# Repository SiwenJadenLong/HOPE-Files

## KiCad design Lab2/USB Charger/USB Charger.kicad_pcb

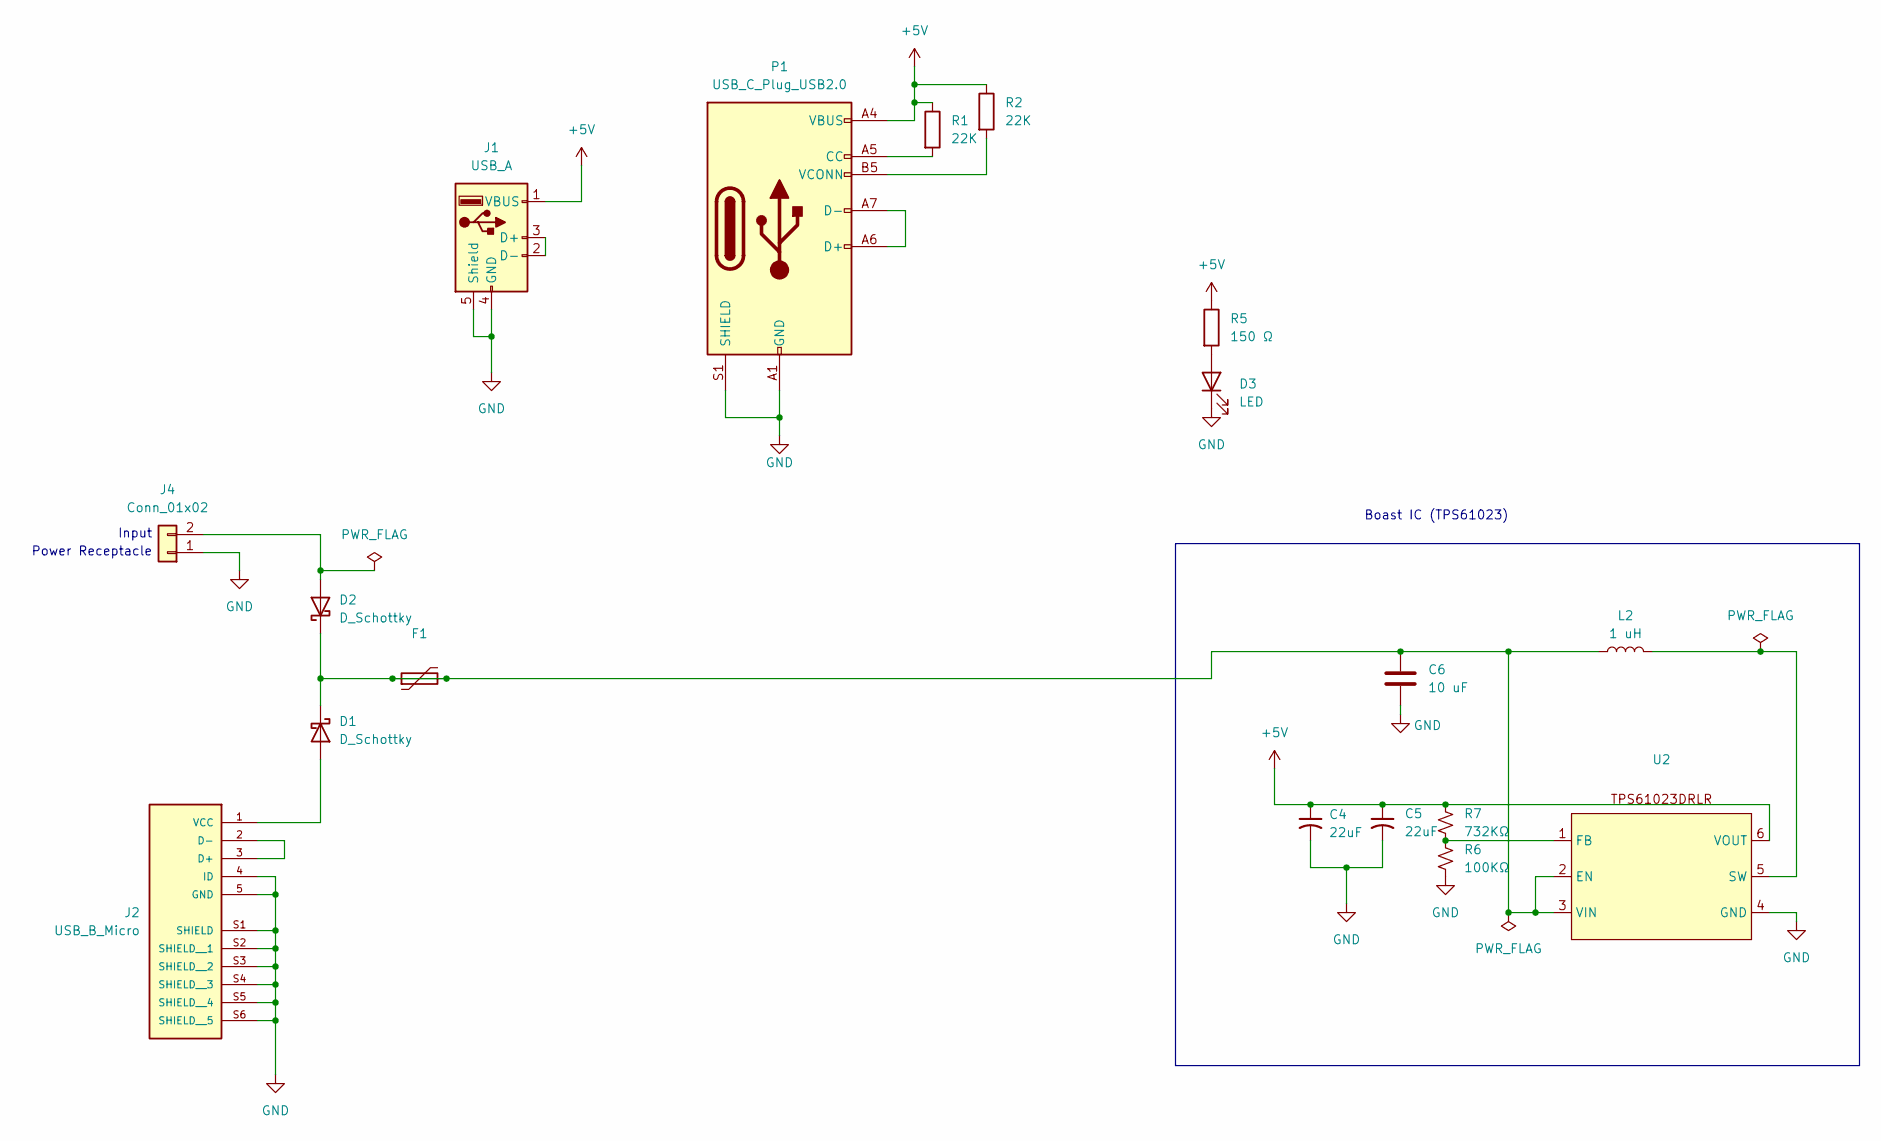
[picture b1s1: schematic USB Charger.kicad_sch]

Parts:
C4, C5: 22uF; C_0603_1608Metric_Pad1.08x0.95mm_HandSolder
C6: 10 uF; C_0402_1005Metric
D1, D2: D_Schottky; D_SMA-SMB_Universal_Handsoldering
D3: LED; LED_0805_2012Metric_Pad1.15x1.40mm_HandSolder
F1: Polyfuse; Fuse_1812_4532Metric_Pad1.30x3.40mm_HandSolder
J1: USB_A; USB_A_Receptacle_GCT_USB1046
J2: USB_B_Micro; AMPHENOL_10118192-0002LF; PARTREV B
J4: Conn_01x02; PinHeader_1x02_P2.54mm_Vertical
L2: 1 uH; SRP6540-1R0M
P1: USB_C_Plug_USB2.0; USB_C_Receptacle_GCT_USB4105-xx-A_16P_TopMnt_Horizontal
R1, R2: 22K; R_0603_1608Metric
R5: 150 Ω; R_0805_2012Metric
R6: 100KΩ; R_0402_1005Metric
R7: 732KΩ; R_0402_1005Metric
U2: SOT-666

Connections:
+5V: C4.1, C5.1, J1.1 (VBUS), P1.A4 (VBUS), P1.A9 (VBUS), P1.B4 (VBUS), P1.B9 (VBUS), R1.1, R2.1, R5.1, R7.1, U2.6 (VOUT)
GND: C4.2, C5.2, C6.2, D3.1 (K), J1.4 (GND), J1.5 (Shield), J2.4 (ID), J2.5 (GND), J2.S1 (SHIELD), J2.S2 (SHIELD__1), J2.S3 (SHIELD__2), J2.S4 (SHIELD__3), J2.S5 (SHIELD__4), J2.S6 (SHIELD__5), J4.1, P1.A1 (GND), P1.A12 (GND), P1.B1 (GND), P1.B12 (GND), P1.S1 (SHIELD), R6.2, U2.4 (GND)
unnamed: D1.2 (A), J2.1 (VCC)
unnamed: C6.1, D1.1 (K), D2.1 (K), F1.1, F1.2, L2.1, U2.2 (EN), U2.3 (VIN)
unnamed: D2.2 (A), J4.2
unnamed: D3.2 (A), R5.2
unnamed: J1.2 (D-), J1.3 (D+)
unnamed: J2.2 (D-), J2.3 (D+)
unnamed: P1.A5 (CC), R1.2
unnamed: P1.A6 (D+), P1.A7 (D-)
unnamed: P1.B5 (VCONN), R2.2
unnamed: R6.1, R7.2, U2.1 (FB)
unnamed: L2.2, U2.5 (SW)

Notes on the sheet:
Input
Power Receptacle
Boast IC (TPS61023)

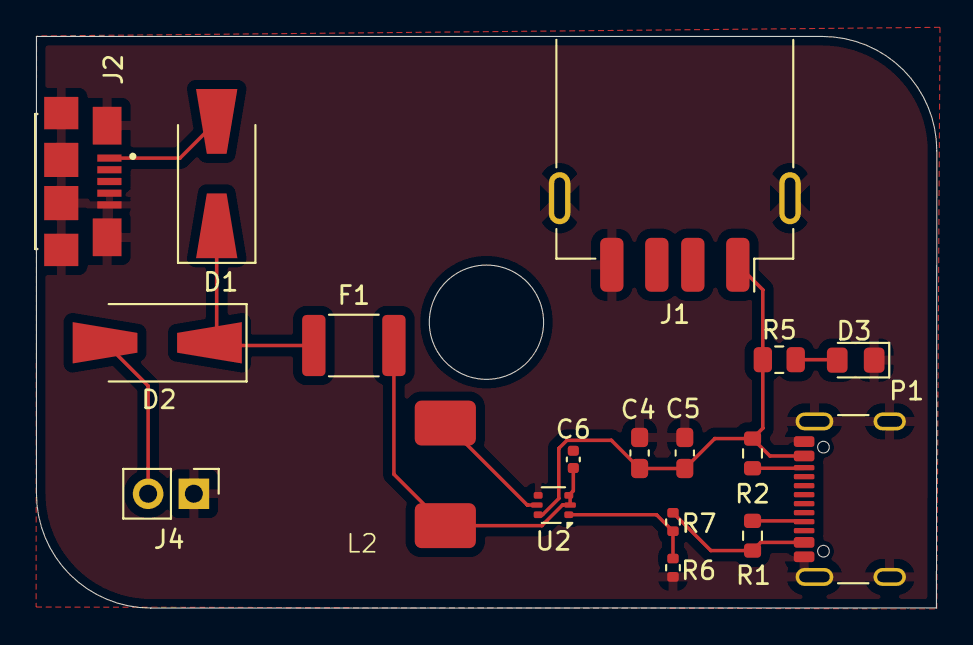
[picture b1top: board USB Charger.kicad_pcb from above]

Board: 2 copper layers, 50.0 x 31.8 mm, 18 parts (0 on the bottom side), 13 nets.

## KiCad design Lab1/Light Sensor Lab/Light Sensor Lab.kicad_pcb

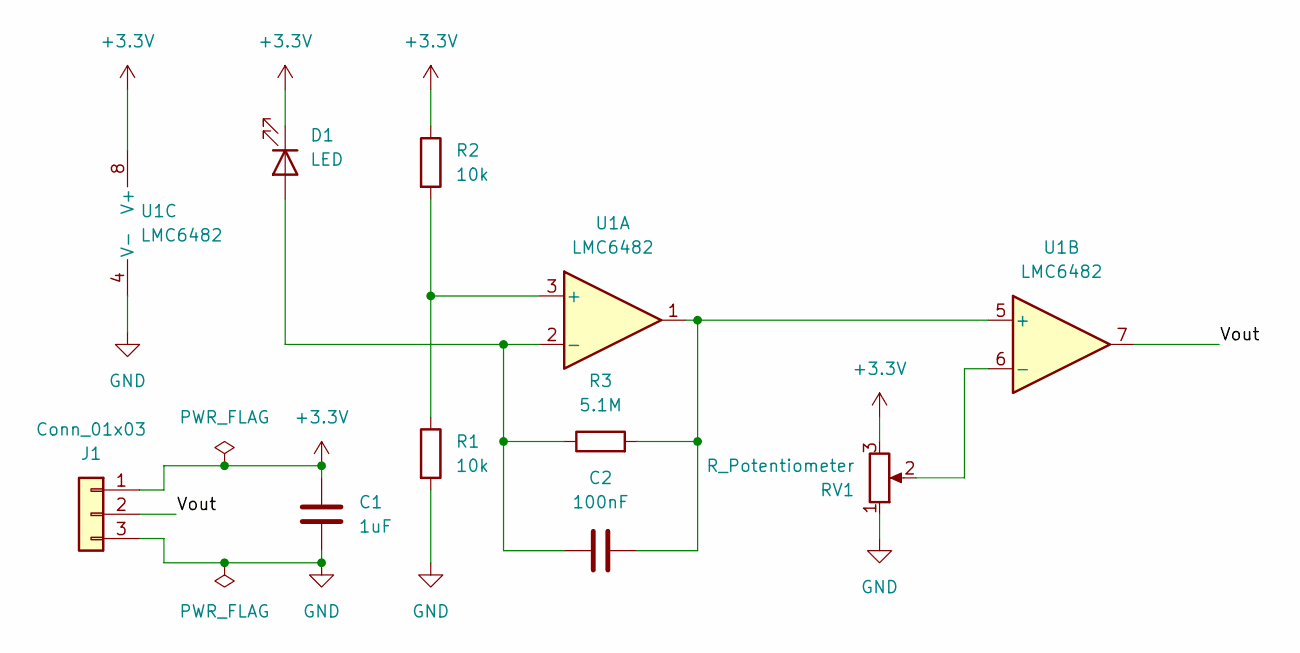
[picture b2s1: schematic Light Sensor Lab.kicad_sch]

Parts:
C1: 1uF; C_0805_2012Metric
C2: 100nF; C_0805_2012Metric
D1: LED; LED_D5.0mm
J1: Conn_01x03; PinSocket_1x03_P2.54mm_Vertical
R1, R2: 10k; R_Axial_DIN0207_L6.3mm_D2.5mm_P7.62mm_Horizontal
R3: 5.1M; R_Axial_DIN0207_L6.3mm_D2.5mm_P7.62mm_Horizontal
RV1: R_Potentiometer; Potentiometer_Vishay_T7-YA_Single_Vertical
U1: LMC6482; SOIC-8_3.9x4.9mm_P1.27mm

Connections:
+3.3V: C1.1, D1.1 (K), J1.1, R2.1, RV1.3, U1.8 (V+)
/Vout: J1.2, U1.7
GND: C1.2, J1.3, R1.2, RV1.1, U1.4 (V-)
unnamed: C2.1, D1.2 (A), R3.1, U1.2 (-)
unnamed: R1.1, R2.2, U1.3 (+)
unnamed: C2.2, R3.2, U1.1, U1.5 (+)
unnamed: RV1.2, U1.6 (-)

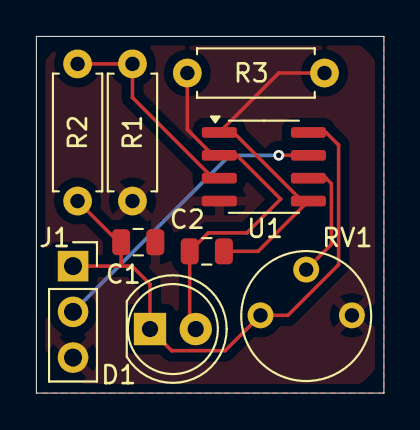
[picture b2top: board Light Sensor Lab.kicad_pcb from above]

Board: 2 copper layers, 19.3 x 19.8 mm, 9 parts (0 on the bottom side), 7 nets.

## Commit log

2025-09-12 Light Sensor schematic created
2025-09-12 added PWR_FLAG for ERC
2025-09-12 Finished Schematic And Checked Off
2025-09-13 PCB Layout done, DRC Approved, Awaiting Checkoff
2025-09-14 small trace tweeks
2025-09-14 small trace tweeks^2
2025-09-19 Lab2: USB Components, Completed
2025-09-19 Made light sensor slightly smaller
2025-09-26 finished USB Charger Schematic, awaiting checkoff
2025-10-03 Finished USB Charger Schematic
2025-10-31 Finished USB Charger Layout, awaiting checkoff
